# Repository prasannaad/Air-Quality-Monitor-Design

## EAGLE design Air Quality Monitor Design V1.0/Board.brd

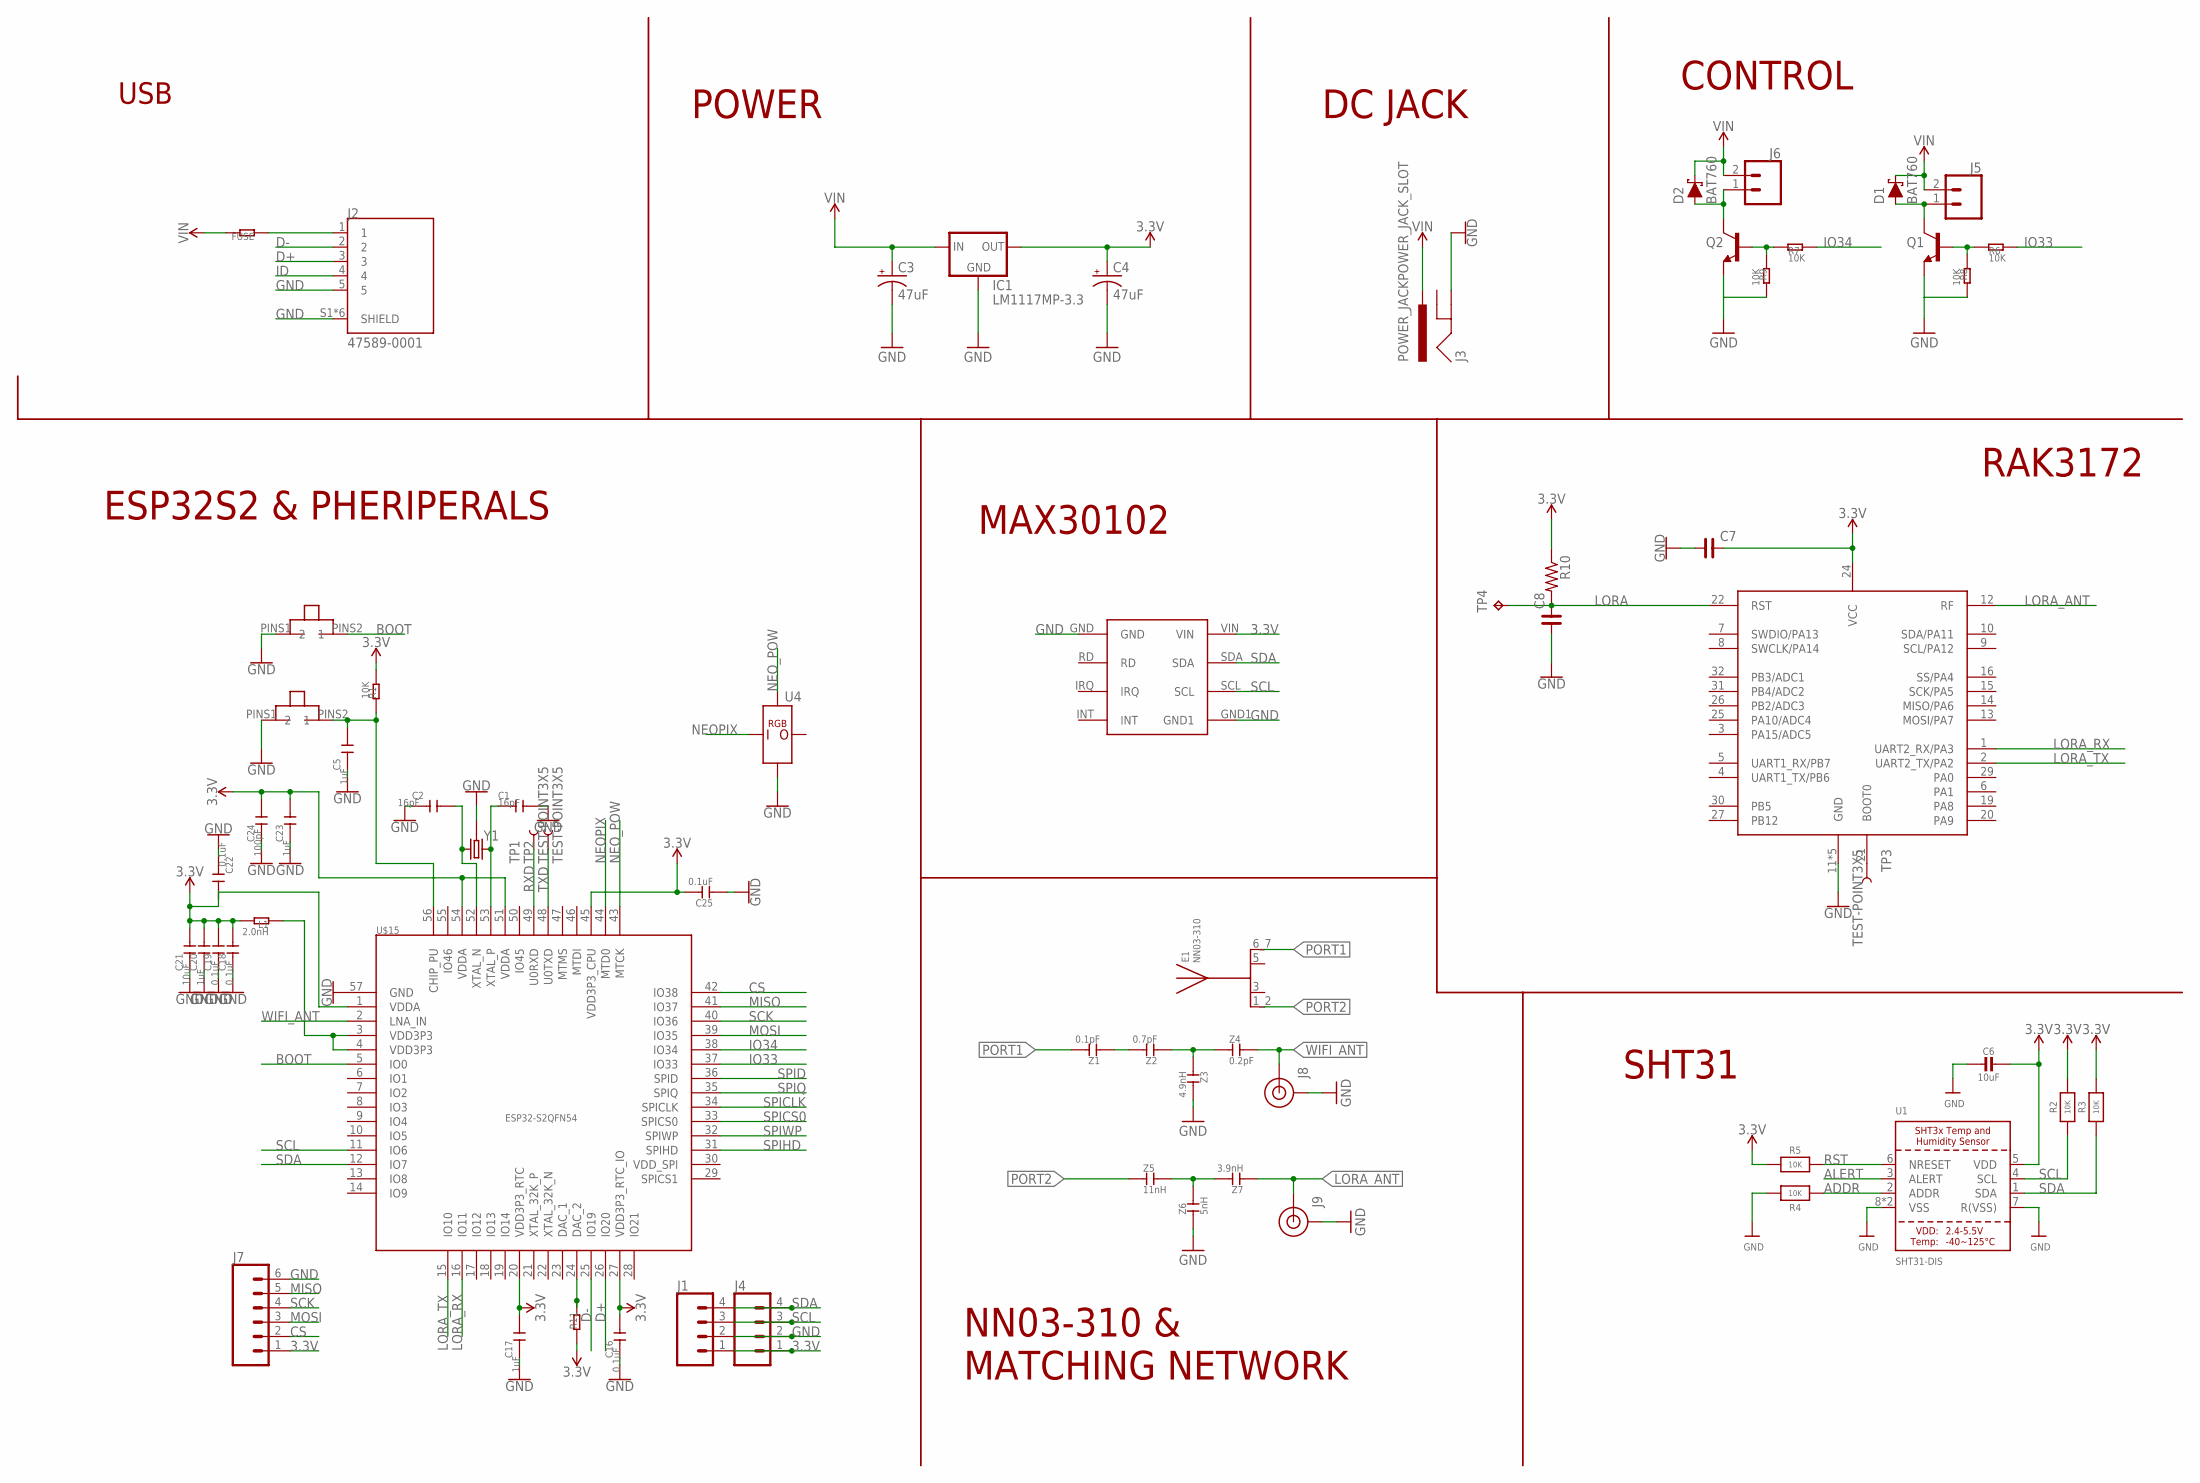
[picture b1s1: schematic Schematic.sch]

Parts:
C1, C2: 16pF; C0603
C3, C4: 47uF; EIA3216
C5, C17, C20, C23: 1uF; C0603
C6: 10uF; 0805-NO
C7, C8: C_0805; C0805
C16, C18, C19, C22, C25: 0.1uF; C0603
C21: 10uF; C0603
C24: 100pF; C0603
D1, D2: BAT760; SOD-323
E1: NN03-310; XCVR_NN03-310
FUSE: 2.0K; R0603
IC1: LM1117MP-3.3; SOT223
J1, J4: CONN_041X04_NO_SILK; 1X04_NO_SILK
J2: 47589-0001; MOLEX_47589-0001
J3: POWER_JACKPOWER_JACK_SLOT; POWER_JACK_PTH_SLOT
J5, J6: CONN_021X02_NO_SILK; 1X02_NO_SILK
J7: CONN_06NO_SILK_FEMALE_PTH; 1X06_NO_SILK
J8, J9: U.FL2PIN-REDUCED-FOOTPRINT; U.FL_REDUCED_FOOTPRINT
L1: 2.0nH; R0603
Q1, Q2: 500mA/300V; SOT23-3
R1, R6, R7, R8, R9, R11: 10K; R0603
R2, R3, R5: 10K; 0805-NO
R4: 10K; _0805MP
R10: CRCW08050000Z0EA; RES_0805
TP1, TP2, TP3: TEST-POINT3X5; PAD.03X.05
TP4: TPTP12R; TP12R
U1: SHT31-DIS; SHT3X
U4: LED-ADDRESSABLE16MM; LED-WS2812B-2020-RING
U$1, U$2: TACTILE
U$3: MAX30102_BREAKOUT; MAX30102
U$4: RAK3172HF; RAK3172
U$15: ESP32-S2QFN54; QFN40P700X700X90-57T400N
Y1: CRYSTAL-GROUNDEDSMD-3.2X2.5; CRYSTAL-SMD-3.2X2.5MM
Z1: 0.1pF; C0603
Z2: 0.7pF; C0603
Z3: 4.9nH; C0603
Z4: 0.2pF; C0603
Z5: 11nH; C0603
Z6: 5nH; C0603
Z7: 3.9nH; C0603

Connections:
3.3V: C4.A (+), C6.1, C7.2, C16.2, C17.2, C18.2, C19.2, C20.2, C21.2, C22.2, C23.2, C24.2, C25.2, IC1.2 (OUT), IC1.4 (OUT), J1.1, J4.1, J7.1, L1.2, R1.2, R2.2, R3.2, R5.1, R10.1, R11.1, U1.5 (VDD), U$3.VIN, U$4.24 (VCC), U$15.1 (VDDA), U$15.20 (VDD3P3_RTC), U$15.27 (VDD3P3_RTC_IO), U$15.45 (VDD3P3_CPU), U$15.51 (VDDA), U$15.54 (VDDA)
ADDR: R4.1, U1.2 (ADDR)
ALERT: U1.3 (ALERT)
BOOT: U$2.PINS2 (2), U$15.5 (IO0)
CS: J7.2, U$15.42 (IO38)
D+: J2.3, U$15.26 (IO20)
D-: J2.2, U$15.25 (IO19)
GND: C1.2, C2.1, C3.C (-), C4.C (-), C5.1, C6.2, C7.1, C8.1, C16.1, C17.1, C18.1, C19.1, C20.1, C21.1, C22.1, C23.1, C24.1, C25.1, IC1.1 (GND), J1.2, J2.5, J2.S1 (SHIELD), J2.S2 (SHIELD), J2.S3 (SHIELD), J2.S4 (SHIELD), J2.S5 (SHIELD), J2.S6 (SHIELD), J3.GND, J4.2, J7.6, J8.1 (GND), J8.2 (GND), J9.1 (GND), J9.2 (GND), Q1.2 (E), Q2.2 (E), R4.2, R8.2, R9.2, U1.7 (R(VSS)), U1.8 (VSS), U1.THERMAL (VSS), U4.GND, U$1.PINS1 (1), U$2.PINS1 (1), U$3.GND, U$3.GND1, U$4.11 (GND), U$4.17 (GND), U$4.18 (GND), U$4.23 (GND), U$4.28 (GND), U$15.57 (GND), Y1.2 (GND), Y1.4 (GND), Z3.2, Z6.1
ID: J2.4
IO33: R6.2, U$15.37 (IO33)
IO34: R7.2, U$15.38 (IO34)
LORA: C8.2, R10.2, TP4.TP, U$4.22 (RST)
LORA_ANT: J9.FEED (SIGNAL), U$4.12 (RF), Z7.1
LORA_RX: U$4.1 (UART2_RX/PA3), U$15.16 (IO11)
LORA_TX: U$4.2 (UART2_TX/PA2), U$15.15 (IO10)
MISO: J7.5, U$15.41 (IO37)
MOSI: J7.3, U$15.39 (IO35)
unnamed: C2.2, U$15.52 (XTAL_N), Y1.3 (2)
unnamed: C1.1, U$15.53 (XTAL_P), Y1.1
unnamed: C5.2, R1.1, U$1.PINS2 (2), U$15.56 (CHIP_PU)
unnamed: L1.1, U$15.3 (VDD3P3), U$15.4 (VDD3P3)
unnamed: Q1.1 (B), R6.1, R8.1
unnamed: FUSE.1, J2.1
unnamed: Q2.1 (B), R7.1, R9.1
unnamed: TP3.P$1, U$4.21 (BOOT0)
unnamed: R11.2, U$15.24 (DAC_2)
unnamed: Z1.1, Z2.2
unnamed: D1.A, J5.1, Q1.3 (C)
unnamed: Z2.1, Z3.1, Z4.1
unnamed: Z5.2, Z6.2, Z7.2
unnamed: D2.A, J6.1, Q2.3 (C)
NEOPIX: U4.DI, U$15.44 (MTD0)
NEO_POW: U4.+ (VDD), U$15.43 (MTCK)
PORT1: E1.6_7 (6), Z1.2
PORT2: E1.1_2 (1), Z5.1
RST: R5.2, U1.6 (NRESET)
RXD: TP1.P$1, U$15.49 (U0RXD)
SCK: J7.4, U$15.40 (IO36)
SCL: J1.3, J4.3, R2.1, U1.4 (SCL), U$3.SCL, U$15.11 (IO6)
SDA: J1.4, J4.4, R3.1, U1.1 (SDA), U$3.SDA, U$15.12 (IO7)
SPICLK: U$15.34 (SPICLK)
SPICS0: U$15.33 (SPICS0)
SPID: U$15.36 (SPID)
SPIHD: U$15.31 (SPIHD)
SPIQ: U$15.35 (SPIQ)
SPIWP: U$15.32 (SPIWP)
TXD: TP2.P$1, U$15.48 (U0TXD)
VDD_SPI: U$15.30 (VDD_SPI)
VIN: C3.A (+), D1.C, D2.C, FUSE.2, IC1.3 (IN), J3.PWR, J5.2, J6.2
WIFI_ANT: J8.FEED (SIGNAL), U$15.2 (LNA_IN), Z4.2

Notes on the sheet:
USB
POWER
DC JACK
CONTROL
ESP32S2 & PHERIPERALS
MAX30102
NN03-310 & MATCHING NETWORK
SHT31
RAK3172

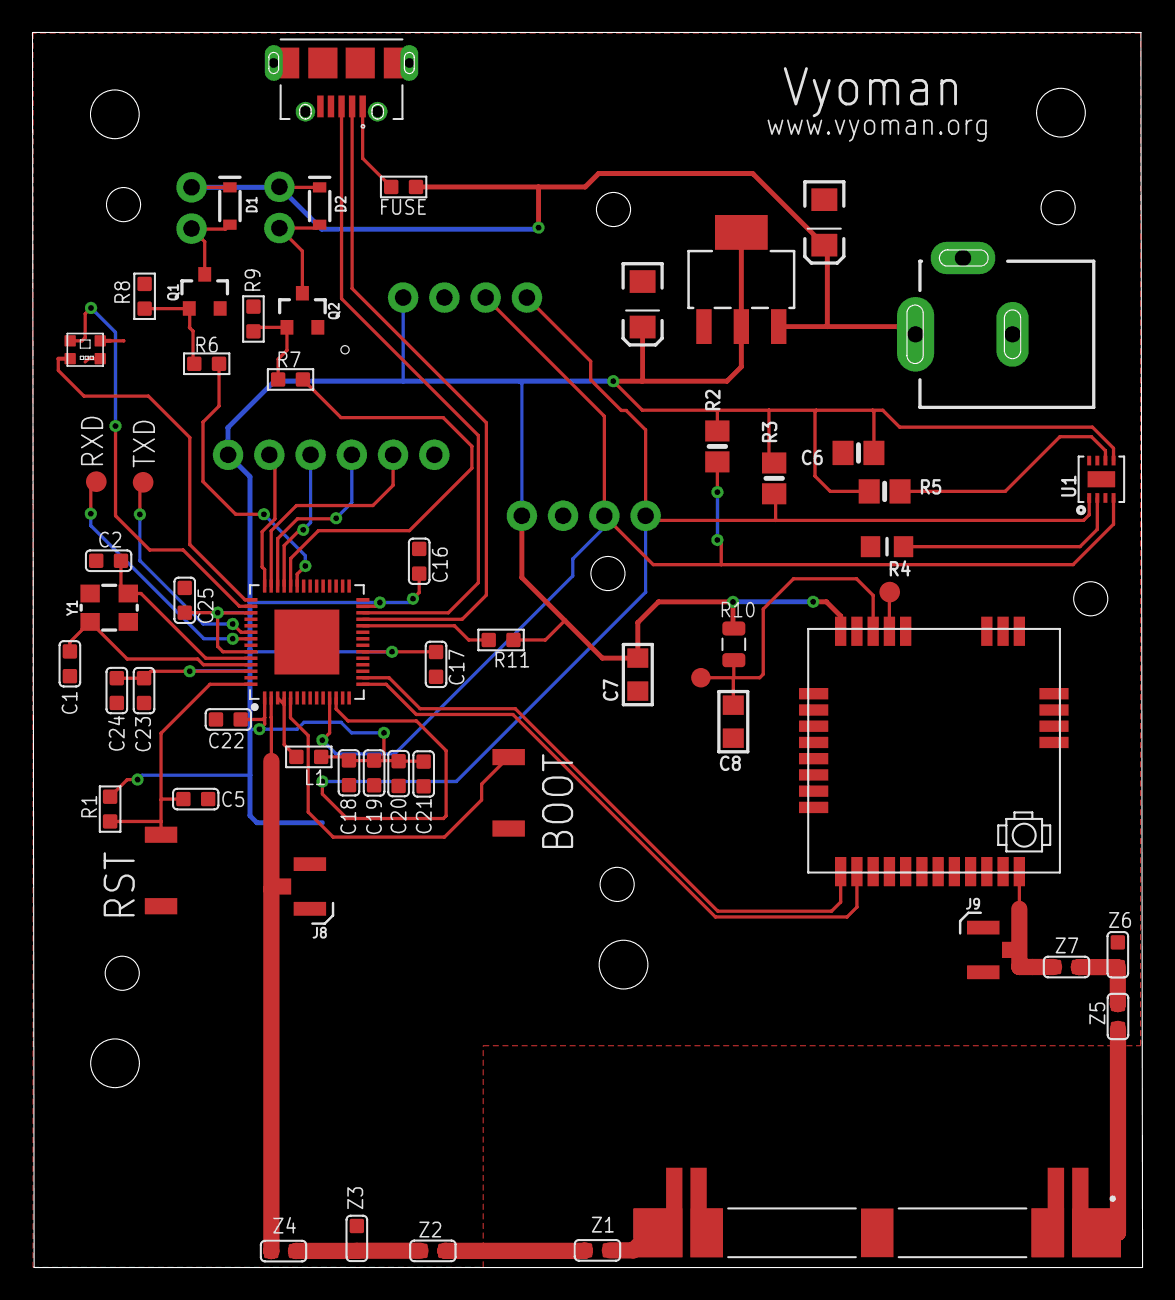
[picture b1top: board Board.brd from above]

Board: 2 copper layers, 68.3 x 76.0 mm, 65 parts (1 on the bottom side), 41 nets.

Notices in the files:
parts and their libraries:
SparkFun-Connectors: Licensing: Creative Commons ShareAlike 4.0 International - https://creativecommons.org/licenses/by-sa/4.0
microbuilder: This work is placed in the public domain, and may be freely used for commercial and non-commercial work with the following conditions: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
